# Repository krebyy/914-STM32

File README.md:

914-STM32
========

The 914-STM32 is a development and prototyping board, based on the ARM Cortex-M0+ 32-bit microcontroller [STM32L053R8T](https://www.st.com/en/microcontrollers-microprocessors/stm32l053r8.html).

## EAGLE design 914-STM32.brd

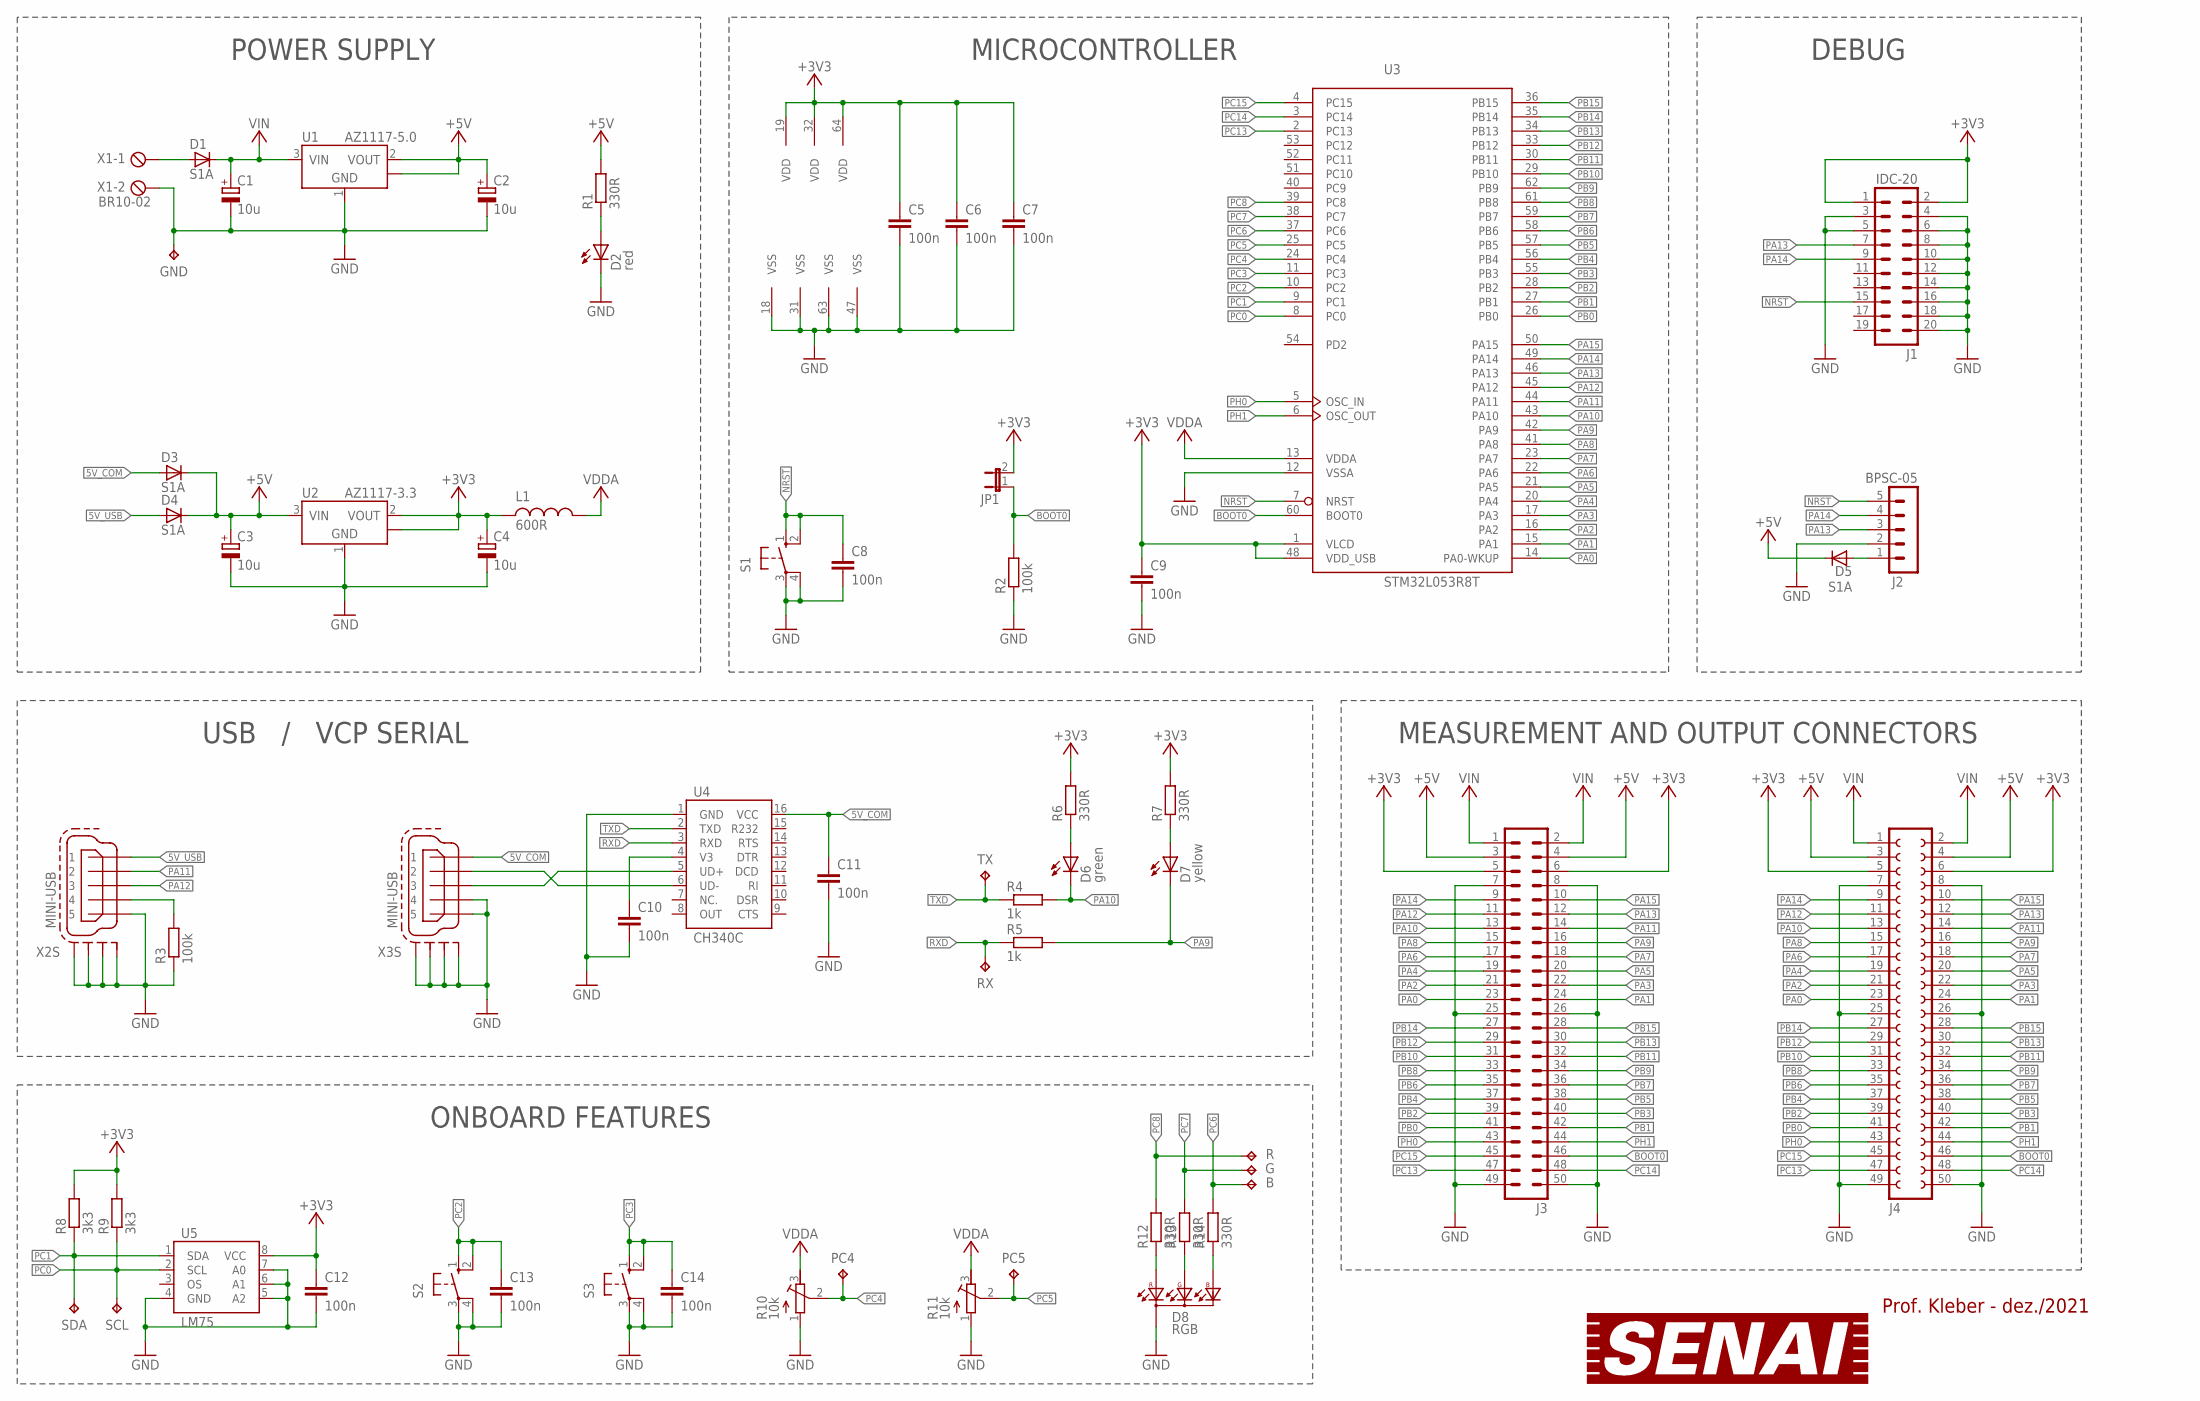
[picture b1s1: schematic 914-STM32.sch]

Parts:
1: GND; TP1
2: SDA; TP1
3: RX; TP1
C1, C2, C3, C4: 10u; CT1206
C5, C6, C7, C8, C9, C10, C11, C12, C13, C14: 100n; C0603
D1, D3, D4, D5: S1A; DO214AC
D2: red; LED-0805
D6: green; LED-0805
D7: yellow; LED-0805
D8: RGB; LED-RGB-5MM
J1: IDC-20; ML20
J2: BPSC-05
J3: MA25-2
J4: FE25-2
JP1: JP1E; JP1
L1: 600R; L0603
R1, R6, R7, R12, R13, R14: 330R; R0603
R2, R3: 100k; R0603
R4, R5: 1k; R0603
R8, R9: 3k3; R0603
R10, R11: 10k; RTRIM3386F
S1, S2, S3: 10-XX; B3F-10XX
TP1: R; TP1
TP2: G; TP1
TP3: SCL; TP1
TP4: PC4; TP1
TP5: PC5; TP1
TP6: B; TP1
TP7: TX; TP1
U1: AZ1117-5.0; SOT223
U2: AZ1117-3.3; SOT223
U3: STM32L053R8T; LQFP64
U4: CH340C; SOIC16
U5: LM75; SOIC8
X1: BR10-02
X2, X3: MINI-USB; 32005-201

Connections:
5V_COM: C11.1, D3.A, U4.16 (VCC), X3.1
5V_USB: D4.A, X2.1
+3V3: C4.+, C5.1, C6.1, C7.1, C9.1, C12.1, J1.1, J1.2, J3.5, J3.6, J4.5, J4.6, JP1.2, L1.2, R6.2, R7.2, R8.2, R9.2, U2.2 (VOUT), U2.4 (TAB), U3.1 (VLCD), U3.19 (VDD), U3.32 (VDD), U3.48 (VDD_USB), U3.64 (VDD), U5.8 (VCC)
+5V: C2.+, C3.+, D3.C, D4.C, D5.C, J3.3, J3.4, J4.3, J4.4, R1.2, U1.2 (VOUT), U1.4 (TAB), U2.3 (VIN)
A_B: D8.4 (ABLUE), R14.1
A_G: D8.3 (AGREEN), R13.1
A_ON: D2.A, R1.1
A_ON1: D6.A, R6.1
A_ON2: D7.A, R7.1
A_R: D8.1 (ARED), R12.1
BOOT0: J3.46, J4.46, JP1.1, R2.2, U3.60 (BOOT0)
GND: 1.TP, C1.-, C2.-, C3.-, C4.-, C5.2, C6.2, C7.2, C8.2, C9.2, C10.2, C11.2, C12.2, C13.2, C14.2, D2.C, D8.2 (C2), J1.3, J1.4, J1.5, J1.6, J1.8, J1.10, J1.12, J1.14, J1.16, J1.18, J1.20, J2.2, J3.7, J3.8, J3.25, J3.26, J3.49, J3.50, J4.7, J4.8, J4.25, J4.26, J4.49, J4.50, R2.1, R3.1, R10.1 (A), R11.1 (A), S1.3, S1.4 (P1), S2.3, S2.4 (P1), S3.3, S3.4 (P1), U1.1 (GND), U2.1 (GND), U3.12 (VSSA), U3.18 (VSS), U3.31 (VSS), U3.47 (VSS), U3.63 (VSS), U4.1 (GND), U5.4 (GND), U5.5 (A2), U5.6 (A1), U5.7 (A0), X1.2, X2.5, X2.M1 (S1), X2.M2 (S2), X2.M3 (S3), X2.M4 (S4), X3.4, X3.5, X3.M1 (S1), X3.M2 (S2), X3.M3 (S3), X3.M4 (S4)
NRST: C8.1, J1.15, J2.5, S1.1 (S), S1.2 (S1), U3.7 (NRST)
PA0: J3.23, J4.23, U3.14 (PA0-WKUP)
PA1: J3.24, J4.24, U3.15 (PA1)
PA2: J3.21, J4.21, U3.16 (PA2)
PA3: J3.22, J4.22, U3.17 (PA3)
PA4: J3.19, J4.19, U3.20 (PA4)
PA5: J3.20, J4.20, U3.21 (PA5)
PA6: J3.17, J4.17, U3.22 (PA6)
PA7: J3.18, J4.18, U3.23 (PA7)
PA8: J3.15, J4.15, U3.41 (PA8)
PA9: D7.C, J3.16, J4.16, R5.2, U3.42 (PA9)
PA10: D6.C, J3.13, J4.13, R4.2, U3.43 (PA10)
PA11: J3.14, J4.14, U3.44 (PA11), X2.2
PA12: J3.11, J4.11, U3.45 (PA12), X2.3
PA13: J1.7, J2.3, J3.12, J4.12, U3.46 (PA13)
PA14: J1.9, J2.4, J3.9, J4.9, U3.49 (PA14)
PA15: J3.10, J4.10, U3.50 (PA15)
PB0: J3.41, J4.41, U3.26 (PB0)
PB1: J3.42, J4.42, U3.27 (PB1)
PB2: J3.39, J4.39, U3.28 (PB2)
PB3: J3.40, J4.40, U3.55 (PB3)
PB4: J3.37, J4.37, U3.56 (PB4)
PB5: J3.38, J4.38, U3.57 (PB5)
PB6: J3.35, J4.35, U3.58 (PB6)
PB7: J3.36, J4.36, U3.59 (PB7)
PB8: J3.33, J4.33, U3.61 (PB8)
PB9: J3.34, J4.34, U3.62 (PB9)
PB10: J3.31, J4.31, U3.29 (PB10)
PB11: J3.32, J4.32, U3.30 (PB11)
PB12: J3.29, J4.29, U3.33 (PB12)
PB13: J3.30, J4.30, U3.34 (PB13)
PB14: J3.27, J4.27, U3.35 (PB14)
PB15: J3.28, J4.28, U3.36 (PB15)
PC0: R9.1, TP3.TP, U3.8 (PC0), U5.2 (SCL)
PC1: 2.TP, R8.1, U3.9 (PC1), U5.1 (SDA)
PC2: C13.1, S2.1 (S), S2.2 (S1), U3.10 (PC2)
PC3: C14.1, S3.1 (S), S3.2 (S1), U3.11 (PC3)
PC4: R10.2 (S), TP4.TP, U3.24 (PC4)
PC5: R11.2 (S), TP5.TP, U3.25 (PC5)
PC6: R14.2, TP6.TP, U3.37 (PC6)
PC7: R13.2, TP2.TP, U3.38 (PC7)
PC8: R12.2, TP1.TP, U3.39 (PC8)
PC13: J3.47, J4.47, U3.2 (PC13)
PC14: J3.48, J4.48, U3.3 (PC14)
PC15: J3.45, J4.45, U3.4 (PC15)
PH0: J3.43, J4.43, U3.5 (OSC_IN)
PH1: J3.44, J4.44, U3.6 (OSC_OUT)
RXD: 3.TP, R5.1, U4.3 (RXD)
SWD_5V: D5.A, J2.1
TXD: R4.1, TP7.TP, U4.2 (TXD)
UD+: U4.5 (UD+), X3.3
UD-: U4.6 (UD-), X3.2
USB_ID: R3.2, X2.4
V3: C10.1, U4.4 (V3)
VDDA: L1.1, R10.3 (E), R11.3 (E), U3.13 (VDDA)
VIN: C1.+, D1.C, J3.1, J3.2, J4.1, J4.2, U1.3 (VIN)
VIN_CONN: D1.A, X1.1

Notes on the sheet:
ONBOARD FEATURES
USB / VCP SERIAL
POWER SUPPLY
MICROCONTROLLER
DEBUG
MEASUREMENT AND OUTPUT CONNECTORS
Prof. Kleber - dez./2021

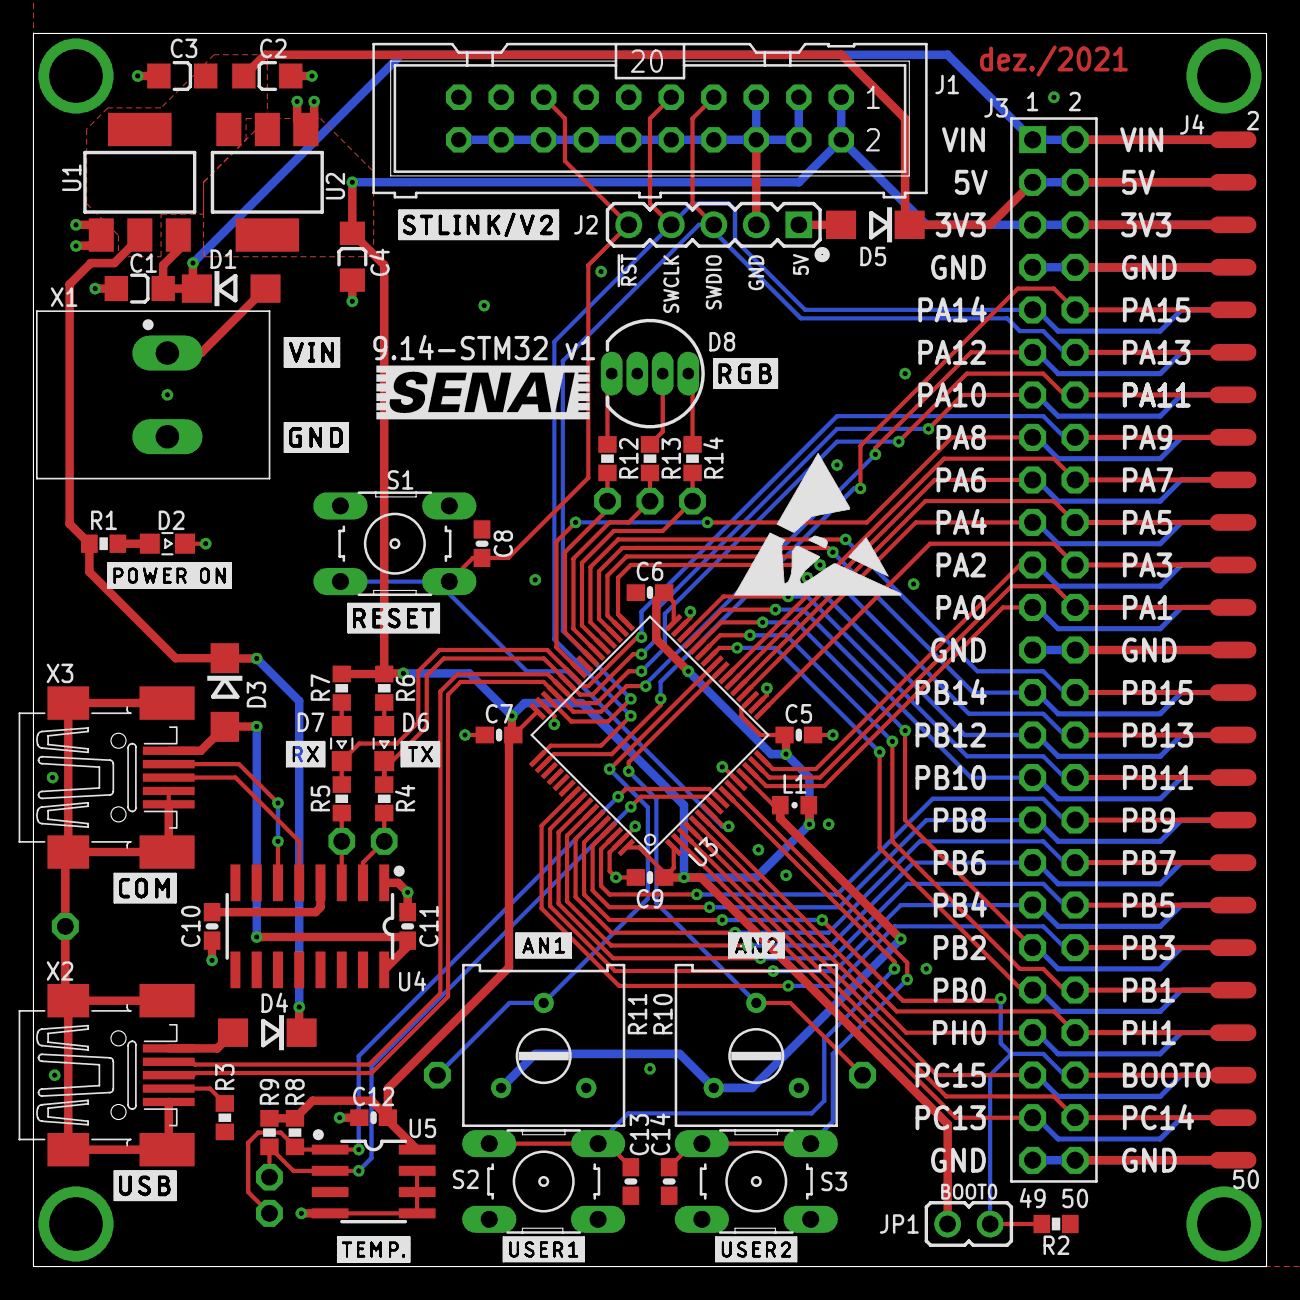
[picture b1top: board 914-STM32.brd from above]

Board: 2 copper layers, 73.7 x 73.7 mm, 64 parts (1 on the bottom side), 69 nets.

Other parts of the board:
U$1: ESD_10.00

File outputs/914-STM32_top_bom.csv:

Comment,Designator,Footprint,LCSC Part #
1k,J4 R4 R5,R0603,
3k3,R8 R9,R0603,
10u,C1 C2 C3 C4,CT1206,
100k,R2 R3,R0603,
100n,C5 C6 C7 C8 C9 C10 C11 C12 C13 C14,C0603,
330R,R1 R6 R7 R12 R13 R14,R0603,
600R,L1,L0603,
AZ1117-3.3,U2,SOT223,
AZ1117-5.0,U1,SOT223,
CH340C,U4,SOIC16,
LM75,U5,SOIC8,
MINI-USB,X2 X3,32005-201,
S1A,D1 D3 D4 D5,DO214AC,
STM32L053R8T,U3,LQFP64,
green,D6,LED-0805,
red,D2,LED-0805,
yellow,D7,LED-0805,
